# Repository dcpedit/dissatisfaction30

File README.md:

# Dissatisfaction30 Macropad

Here you will find all the source files I used for my build.

[Keyboard Layout Editor (KLE)](http://www.keyboard-layout-editor.com/#/gists/a50e7cce1739c047275b94c15fb516cc)

# Image Gallery
https://imgur.com/a/5sZTefW

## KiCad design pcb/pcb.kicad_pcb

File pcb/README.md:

# Dissatisfaction30 PCB

To get the PCB manufactured, upload `dissat-pcb.zip` to [JLCPCB](https://jlcpcb.com), select your desired PCB color while keeping all the other default options, and place your order (minimum 5).  If you made tweaks to the PCB in KiCad, follow [this tutorial](https://support.jlcpcb.com/article/194-how-to-generate-gerber-and-drill-files-in-kicad-6) to generate new Gerber files

## Requied Components
| Name                   | Qty | Notes |
| ---------              | --- | ----- |
| Elite-C controller     | 1   | Soldered directly onto PCB
| SSD1306 128x32 OLED    | 1   |
| EC11 rotary encoder    | 1   |
| Key switches           | 30  |
| 3u stabalizer          | 1   |
| 2u stabalizer          | 1   |
| OLED header (1x4)      | 1   | [Link](https://www.mouser.com/ProductDetail/517-929850-01-04-RA)
| Kailh hot swap socket  | 30  | [Link](https://www.aliexpress.com/item/2255800865526224.html?spm=a2g0o.order_list.0.0.71e51802oef56x&gatewayAdapt=4itemAdapt)
| BAV70 SMD diode        | 16  | [Link](https://www.digikey.com/en/products/detail/onsemi/BAV70LT3G/1475508)

You will need to sand the OLED header down so that the plastic is about 7mm in height (not including the pins).  Also remove any plastic spacers on the OLED pins, and make sure the pins insert fully into the now shorter header.  If it doesn't sit flush with the OLED PCB, cut the OLED pins a bit shorter until it does.

It is also possible to replace the Elite-C with a nice!nano for wireless support or a Pro-Micro since the bottom 5 pins are not used.  But the included case design expects the controler to be soldered directly onto the PCB, so using a controller that requires low-profile sockets (I suggest Mill-Max 315-43-112-41-003000) will also require a change to the case to allow for the extra height.  Try cutting out a space below the controller on layer `#8` (similar to layer `#7`)

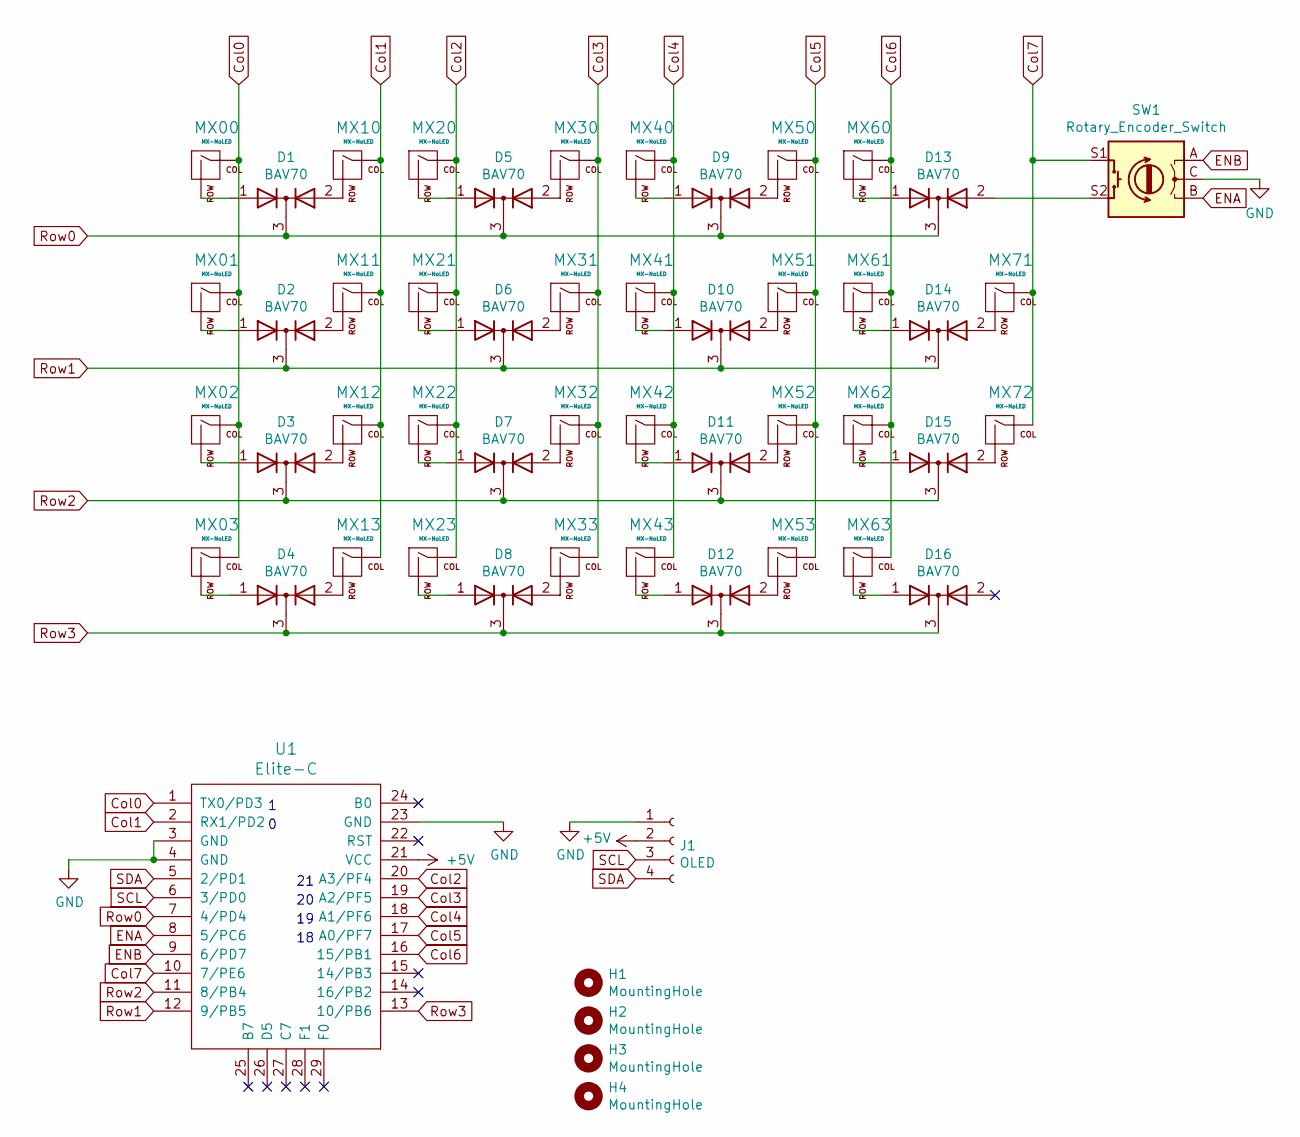
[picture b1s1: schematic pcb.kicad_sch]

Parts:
D1, D2, D3, D4, D5, D6, D7, D8, D9, D10, D11, D12, D13, D14, D15, D16: BAV70; SOT-23_Handsoldering
H1, H2, H3, H4: MountingHole; MountingHole_2.2mm_M2_Pad
J1: OLED; SSD1306_OLED
MX00, MX10, MX11, MX12, MX13, MX20, MX21, MX22, MX23, MX30, MX31, MX32, MX33, MX40, MX41, MX42, MX43, MX50, MX51, MX52, MX53, MX60, MX61, MX62, MX63, MX71, MX72: MX-NoLED; MXOnly-1U-Hotswap
MX01: MX-NoLED; MXOnly-1.5U-Hotswap
MX02: MX-NoLED; MXOnly-1.75U-Hotswap
MX03: MX-NoLED; MXOnly-2.25U-Hotswap
SW1: Rotary_Encoder_Switch; RotaryEncoder_Alps_EC11E-Switch_Vertical_H20mm
U1: Elite-C

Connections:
+5V: J1.2, U1.21 (VCC)
Col0: MX00.1 (COL), MX01.1 (COL), MX02.1 (COL), MX03.1 (COL), U1.1 (TX0/PD3)
Col1: MX10.1 (COL), MX11.1 (COL), MX12.1 (COL), MX13.1 (COL), U1.2 (RX1/PD2)
Col2: MX20.1 (COL), MX21.1 (COL), MX22.1 (COL), MX23.1 (COL), U1.20 (A3/PF4)
Col3: MX30.1 (COL), MX31.1 (COL), MX32.1 (COL), MX33.1 (COL), U1.19 (A2/PF5)
Col4: MX40.1 (COL), MX41.1 (COL), MX42.1 (COL), MX43.1 (COL), U1.18 (A1/PF6)
Col5: MX50.1 (COL), MX51.1 (COL), MX52.1 (COL), MX53.1 (COL), U1.17 (A0/PF7)
Col6: MX60.1 (COL), MX61.1 (COL), MX62.1 (COL), MX63.1 (COL), U1.16 (15/PB1)
Col7: MX71.1 (COL), MX72.1 (COL), SW1.S1, U1.10 (7/PE6)
ENA: SW1.B, U1.8 (5/PC6)
ENB: SW1.A, U1.9 (6/PD7)
GND: J1.1, SW1.C, U1.3 (GND), U1.4 (GND), U1.23 (GND)
unnamed: D1.1 (A), MX00.2 (ROW)
unnamed: D1.2 (A), MX10.2 (ROW)
unnamed: D2.1 (A), MX01.2 (ROW)
unnamed: D2.2 (A), MX11.2 (ROW)
unnamed: D3.1 (A), MX02.2 (ROW)
unnamed: D3.2 (A), MX12.2 (ROW)
unnamed: D4.1 (A), MX03.2 (ROW)
unnamed: D4.2 (A), MX13.2 (ROW)
unnamed: D5.1 (A), MX20.2 (ROW)
unnamed: D5.2 (A), MX30.2 (ROW)
unnamed: D6.1 (A), MX21.2 (ROW)
unnamed: D6.2 (A), MX31.2 (ROW)
unnamed: D7.1 (A), MX22.2 (ROW)
unnamed: D7.2 (A), MX32.2 (ROW)
unnamed: D8.1 (A), MX23.2 (ROW)
unnamed: D8.2 (A), MX33.2 (ROW)
unnamed: D9.1 (A), MX40.2 (ROW)
unnamed: D9.2 (A), MX50.2 (ROW)
unnamed: D10.1 (A), MX41.2 (ROW)
unnamed: D10.2 (A), MX51.2 (ROW)
unnamed: D11.1 (A), MX42.2 (ROW)
unnamed: D11.2 (A), MX52.2 (ROW)
unnamed: D12.1 (A), MX43.2 (ROW)
unnamed: D12.2 (A), MX53.2 (ROW)
unnamed: D13.1 (A), MX60.2 (ROW)
unnamed: D13.2 (A), SW1.S2
unnamed: D14.1 (A), MX61.2 (ROW)
unnamed: D14.2 (A), MX71.2 (ROW)
unnamed: D15.1 (A), MX62.2 (ROW)
unnamed: D15.2 (A), MX72.2 (ROW)
unnamed: D16.1 (A), MX63.2 (ROW)
Row0: D1.3 (K), D5.3 (K), D9.3 (K), D13.3 (K), U1.7 (4/PD4)
Row1: D2.3 (K), D6.3 (K), D10.3 (K), D14.3 (K), U1.12 (9/PB5)
Row2: D3.3 (K), D7.3 (K), D11.3 (K), D15.3 (K), U1.11 (8/PB4)
Row3: D4.3 (K), D8.3 (K), D12.3 (K), D16.3 (K), U1.13 (10/PB6)
SCL: J1.3, U1.6 (3/PD0)
SDA: J1.4, U1.5 (2/PD1)

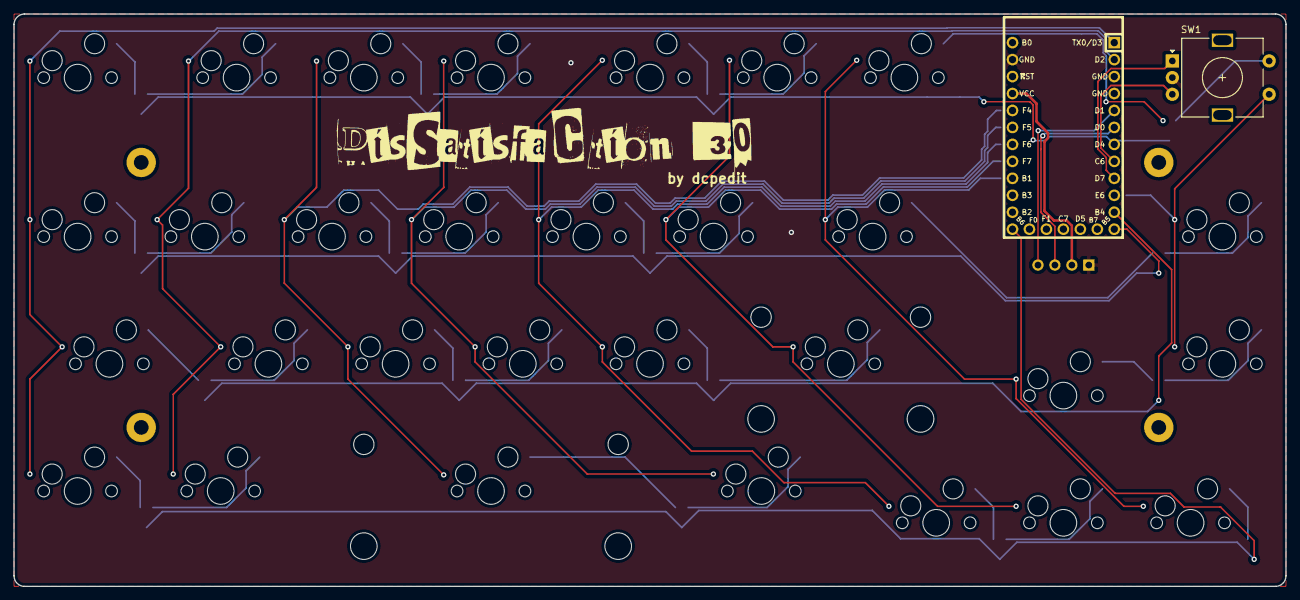
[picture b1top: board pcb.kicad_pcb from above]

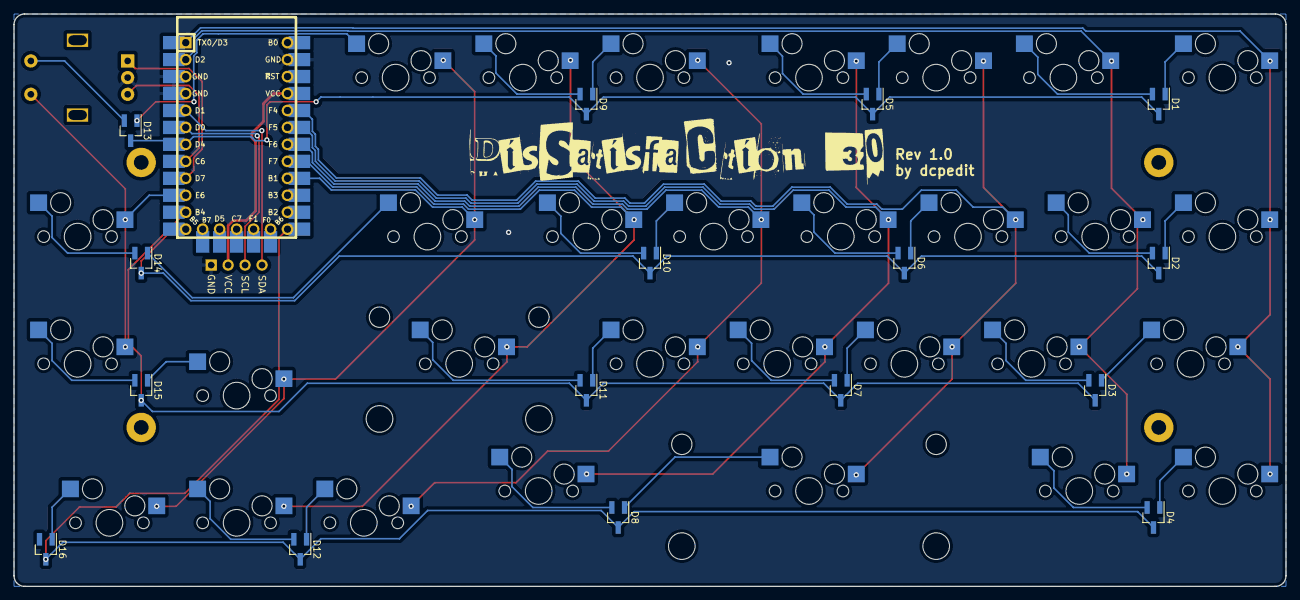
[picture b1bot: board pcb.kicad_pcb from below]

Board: 2 copper layers, 190.5 x 85.7 mm, 53 parts (17 on the bottom side), 49 nets.

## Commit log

2022-08-24 Readme and license file
2022-08-30 Readme and cleanup for case
2022-08-30 Ignore muse
2022-08-30 Remove temp file
2022-08-31 PCB readme
2022-08-31 Fix typos
2022-08-31 Add dxf file
2022-08-31 Add missing info in readmes
2022-09-10 Update README.md
    Add images
2022-09-10 Format images
2022-09-19 Add firmware
2022-09-19 Fix typo
2022-09-21 Fix firmware hex
2022-10-16 Fix screw sizes
2022-10-18 Fix standoff size
2022-11-18 Update README.md
    Correct standoff size
2023-01-13 add 3d printed case files
2023-01-13 fix images in readme
